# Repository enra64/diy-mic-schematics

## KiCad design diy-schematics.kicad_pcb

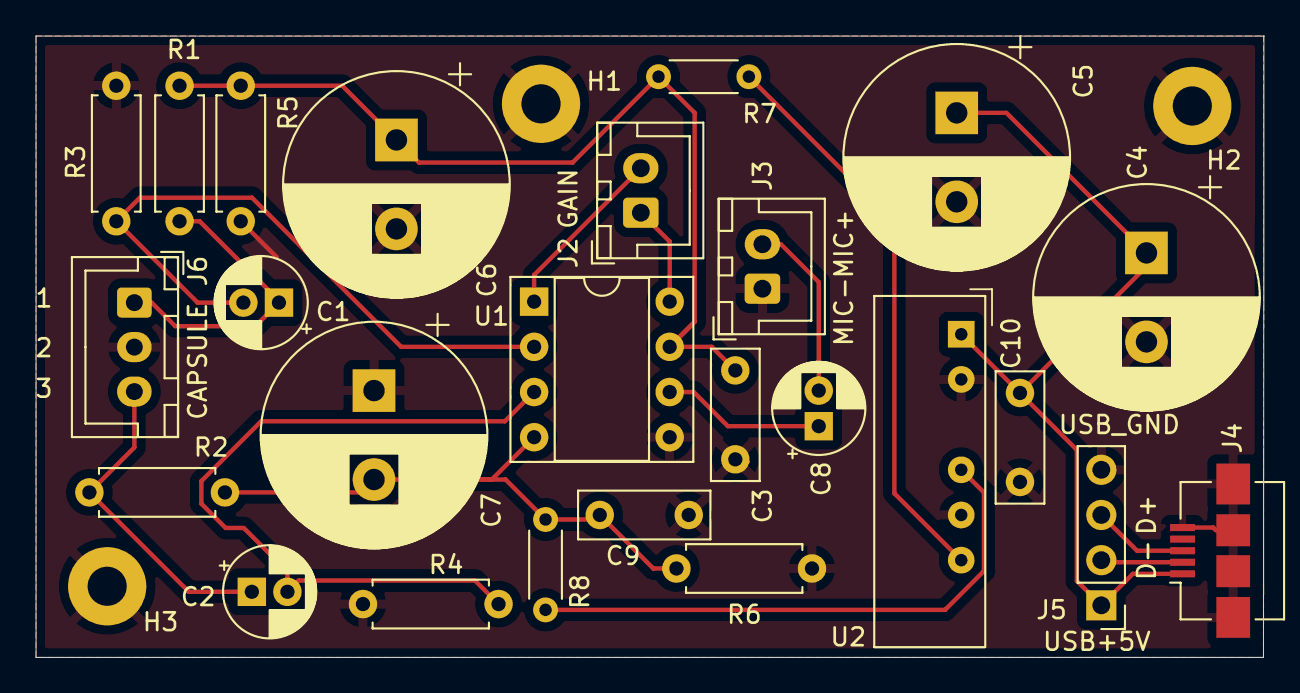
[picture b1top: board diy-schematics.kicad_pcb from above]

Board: 2 copper layers, 69.0 x 34.9 mm, 28 parts (0 on the bottom side), 16 nets.

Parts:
C1, C2, C8: 22uF; CP_Radial_D5.0mm_P2.00mm
C3, C9, C10: 100n; C_Rect_L7.2mm_W2.5mm_P5.00mm_FKS2_FKP2_MKS2_MKP2
C4, C5: 2200uF; CP_Radial_D12.5mm_P5.00mm
C6, C7: 2200uF 16V; CP_Radial_D12.5mm_P5.00mm
H1, H2, H3: MountingHole_Pad; MountingHole_2.2mm_M2_Pad
J2: GAINCON; JST_XH_B2B-XH-A_1x02_P2.50mm_Vertical
J3: Conn_01x02_Female; JST_XH_B2B-XH-A_1x02_P2.50mm_Vertical
J4: USB_SOK; USB_Micro-B_Amphenol_10104110_Horizontal
J5: USB_CON; PinHeader_1x04_P2.54mm_Vertical
J6: MIC_CON1; JST_XH_B3B-XH-A_1x03_P2.50mm_Vertical
R1, R2, R5, R6: 2.2kΩ; R_Axial_DIN0207_L6.3mm_D2.5mm_P7.62mm_Horizontal
R3, R4: 3.9kΩ; R_Axial_DIN0207_L6.3mm_D2.5mm_P7.62mm_Horizontal
R7, R8: 100Ω; R_Axial_DIN0204_L3.6mm_D1.6mm_P5.08mm_Horizontal
U1: THAT1512PO8-U1; DIP-8_W7.62mm_Socket
U2: NMA0515SC; Converter_DCDC_muRata_NMAxxxxSC_THT

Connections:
+15V: R7.2, U2.6 (VOUT+)
-15V: R8.2, U2.4 (VOUT-)
Earth: C3.2, C4.2, C5.2, C6.2, C7.1, C9.2, C10.2, H1.1, H2.1, H3.1, J3.1, J4.5 (GND), J4.6 (Shield), J5.4, J6.2, R3.2, R4.2, R5.2, R6.2, U1.5 (REF), U2.2 (VIN-), U2.5 (0V)
unnamed: C1.1, J6.1, R1.1
unnamed: C1.2, R3.1, U1.2 (IN-)
unnamed: C2.1, J6.3, R2.1
unnamed: C2.2, R4.1, U1.3 (IN+)
unnamed: C3.1, C6.1, R1.2, R5.1, R7.1, U1.7 (V+)
unnamed: C7.2, C9.1, R2.2, R6.1, R8.1, U1.4 (V-)
unnamed: C8.1, U1.6 (OUT)
unnamed: C8.2, J3.2
unnamed: J2.1, U1.8 (RG2)
unnamed: J2.2, U1.1 (RG1)
unnamed: J4.2 (D-), J5.2
unnamed: J4.3 (D+), J5.3
VBUS: C4.1, C5.1, C10.1, J4.1 (VBUS), J5.1, U2.1 (VIN+)

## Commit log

2021-12-21 schematics only; initial version
2021-12-24 pcb layout
2022-01-02 misc changes
2022-01-02 FG update
2022-01-02 update footprints
2022-01-02 new PCB design, some minor compat changes in schematics
2022-01-02 fixes to new PCB
2022-01-02 reduce footprint of PCB
2022-01-03 added mounting holes, rendered gerber files
2022-01-03 add matching file to check if BOM is correct
2022-01-03 add JST-XH connectors to BOM file
2022-02-03 new gerber files
2022-02-05 swap MIC+ and MIC-
